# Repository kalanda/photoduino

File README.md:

_                          _       _             
          | |           _            | |     (_)            
     ____ | |__   ___ _| |_  ___   __| |_   _ _ ____   ___  
    |  _ \|  _ \ / _ (_   _)/ _ \ / _  | | | | |  _ \ / _ \ 
    | |_| | | | | |_| || |_| |_| ( (_| | |_| | | | | | |_| |
    |  __/|_| |_|\___/  \__)\___/ \____|____/|_|_| |_|\___/ 
    |_|  THE OPENSOURCE CAMERA CONTROLLER BASED ON ARDUINO                                                         

https://kalanda.github.io/photoduino/

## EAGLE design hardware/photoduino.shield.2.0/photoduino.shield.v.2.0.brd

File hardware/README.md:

_                          _       _             
          | |           _            | |     (_)            
     ____ | |__   ___ _| |_  ___   __| |_   _ _ ____   ___  
    |  _ \|  _ \ / _ (_   _)/ _ \ / _  | | | | |  _ \ / _ \ 
    | |_| | | | | |_| || |_| |_| ( (_| | |_| | | | | | |_| |
    |  __/|_| |_|\___/  \__)\___/ \____|____/|_|_| |_|\___/ 
    |_|  THE OPENSOURCE CAMERA CONTROLLER BASED ON ARDUINO                                                         

#Photoduino hardware

This is the repository for hardware parts of Photoduino.

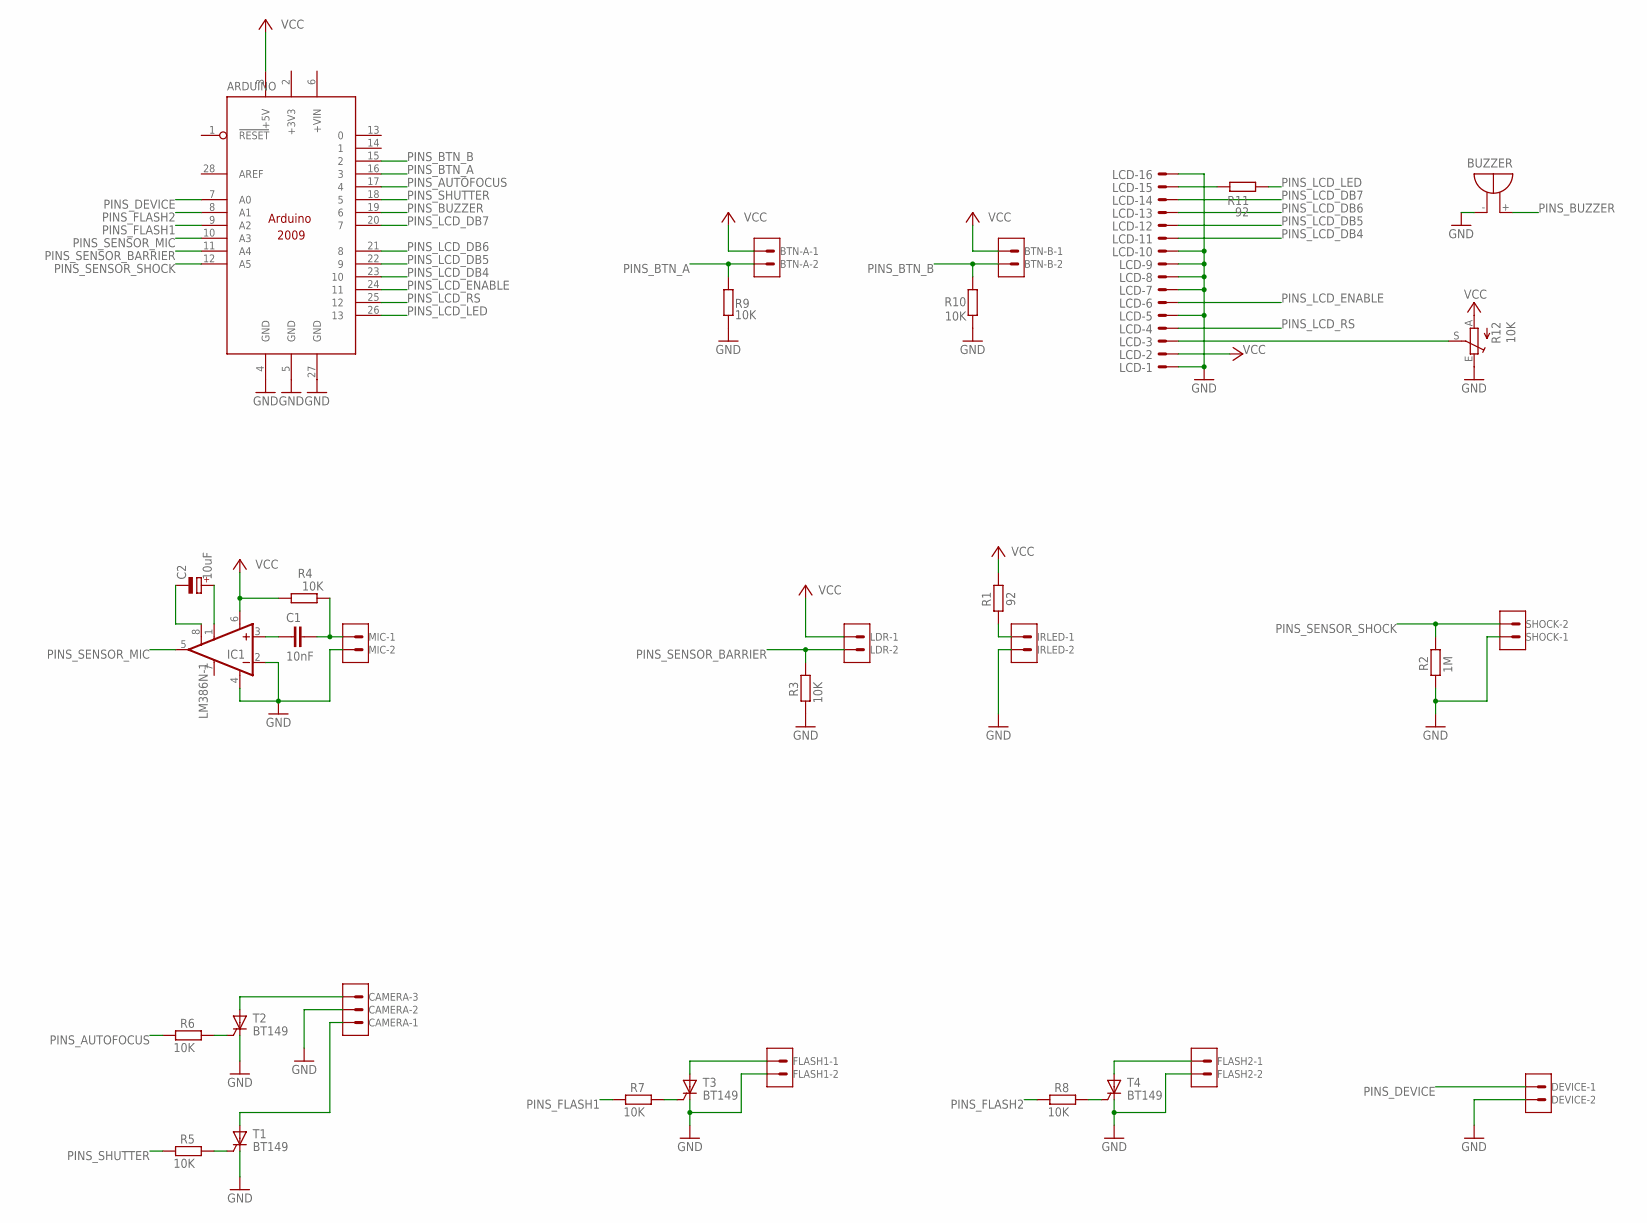
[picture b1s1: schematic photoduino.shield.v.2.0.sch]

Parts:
ARDUINO: ARDUINO2009_11; ARDUINO2009_1
BTN-A: 22-27-2021-02; 6410-02
BTN-B: 22-27-2021-02; 6410-02
BUZZER: F/TMB
C1: 10nF; C050-025X075
C2: 10uF; E2,5-6
CAMERA: 22-27-2031-03; 6410-03
DEVICE: 22-27-2021-02; 6410-02
FLASH1, FLASH2: 22-27-2021-02; 6410-02
IC1: LM386N-1; DIL08
IRLED: 22-27-2021-02; 6410-02
LCD: ML16E; ML16
LDR: 22-27-2021-02; 6410-02
LOGO: LOGOKALANDA
MIC: 22-27-2021-02; 6410-02
R1, R11: 92; 0207/7
R2: 1M; 0207/7
R3, R4, R5, R6, R7, R8, R9, R10: 10K; 0207/7
R12: 10K; RJ9W
SHOCK: 22-27-2021-02; 6410-02
T1, T2, T3, T4: BT149; TO92-4

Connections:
+3V3: ARDUINO.2 (+3V3)
GND: ARDUINO.4 (GND), ARDUINO.5 (GND), ARDUINO.27 (GND), BUZZER.-, CAMERA.2, DEVICE.2, FLASH1.2, FLASH2.2, IC1.2 (-IN), IC1.4 (GND), IRLED.2, LCD.1, LCD.5, LCD.7, LCD.8, LCD.9, LCD.10, LCD.16, MIC.2, R2.2, R3.2, R9.1, R10.2, R12.E, SHOCK.1, T1.C, T2.C, T3.C, T4.C
LCD_CONTRAST: LCD.3, R12.S
unnamed: IRLED.1, R1.2
unnamed: C1.1, IC1.3 (+IN)
unnamed: C1.2, MIC.1, R4.1
unnamed: R7.1, T3.G
unnamed: R8.1, T4.G
unnamed: CAMERA.3, T2.A
unnamed: R6.1, T2.G
unnamed: R5.1, T1.G
unnamed: C2.+, IC1.1 (GAIN)
unnamed: FLASH2.1, T4.A
unnamed: FLASH1.1, T3.A
unnamed: C2.-, IC1.8 (GAIN)
unnamed: LCD.15, R11.2
PINS_AUTOFOCUS: ARDUINO.17 (4), R6.2
PINS_BTN_A: ARDUINO.16 (3), BTN-A.2, R9.2
PINS_BTN_B: ARDUINO.15 (2), BTN-B.2, R10.1
PINS_BUZZER: ARDUINO.19 (6), BUZZER.+
PINS_DEVICE: ARDUINO.7 (A0), DEVICE.1
PINS_FLASH1: ARDUINO.9 (A2), R7.2
PINS_FLASH2: ARDUINO.8 (A1), R8.2
PINS_LCD_DB4: ARDUINO.23 (10), LCD.11
PINS_LCD_DB5: ARDUINO.22 (9), LCD.12
PINS_LCD_DB6: ARDUINO.21 (8), LCD.13
PINS_LCD_DB7: ARDUINO.20 (7), LCD.14
PINS_LCD_ENABLE: ARDUINO.24 (11), LCD.6
PINS_LCD_LED: ARDUINO.26 (13), R11.1
PINS_LCD_RS: ARDUINO.25 (12), LCD.4
PINS_SENSOR_BARRIER: ARDUINO.11 (A4), LDR.2, R3.1
PINS_SENSOR_MIC: ARDUINO.10 (A3), IC1.5 (OUT)
PINS_SENSOR_SHOCK: ARDUINO.12 (A5), R2.1, SHOCK.2
PINS_SHUTTER: ARDUINO.18 (5), R5.2
SHUTTER: CAMERA.1, T1.A
VCC: ARDUINO.3 (+5V), BTN-A.1, BTN-B.1, IC1.6 (VS), LCD.2, LDR.1, R1.1, R4.2, R12.A

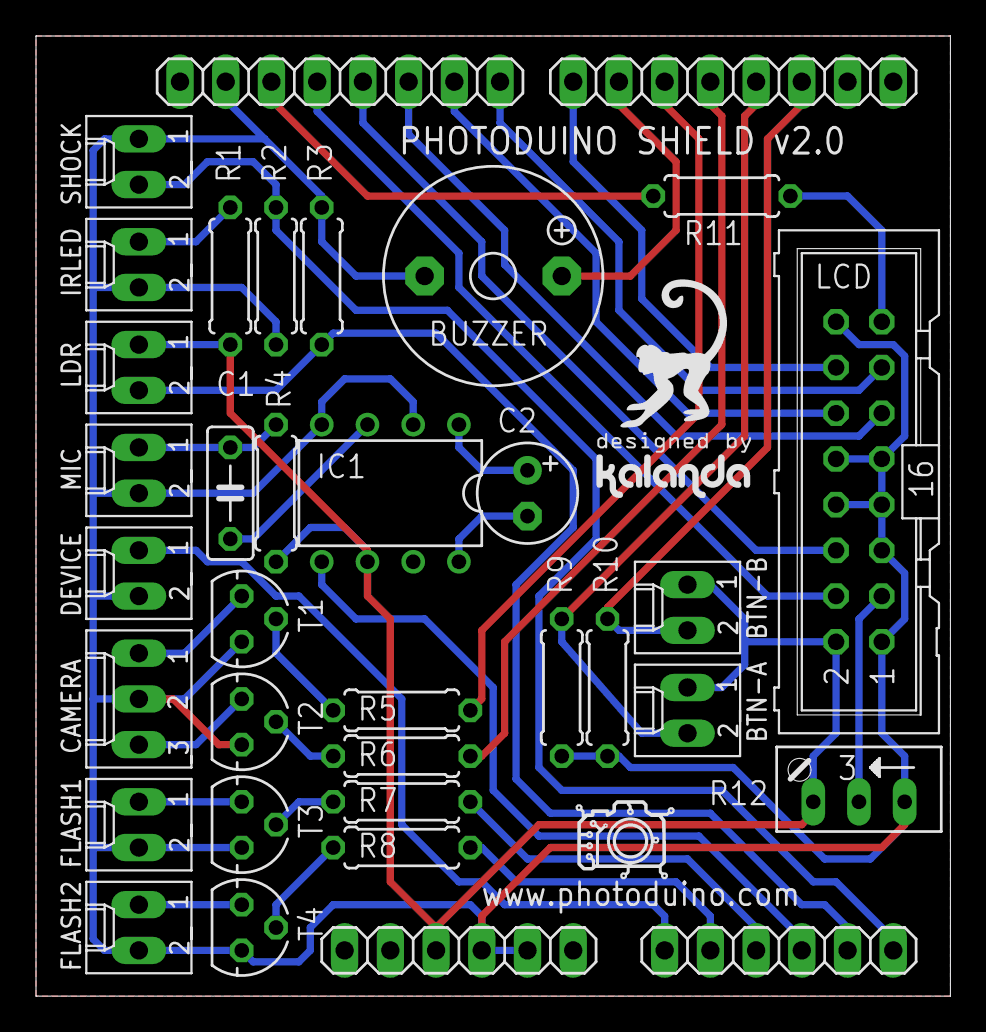
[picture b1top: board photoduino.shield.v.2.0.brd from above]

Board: 2 copper layers, 50.8 x 53.3 mm, 34 parts (0 on the bottom side), 35 nets.

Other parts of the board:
U$1: LOGOPHOTODUINO

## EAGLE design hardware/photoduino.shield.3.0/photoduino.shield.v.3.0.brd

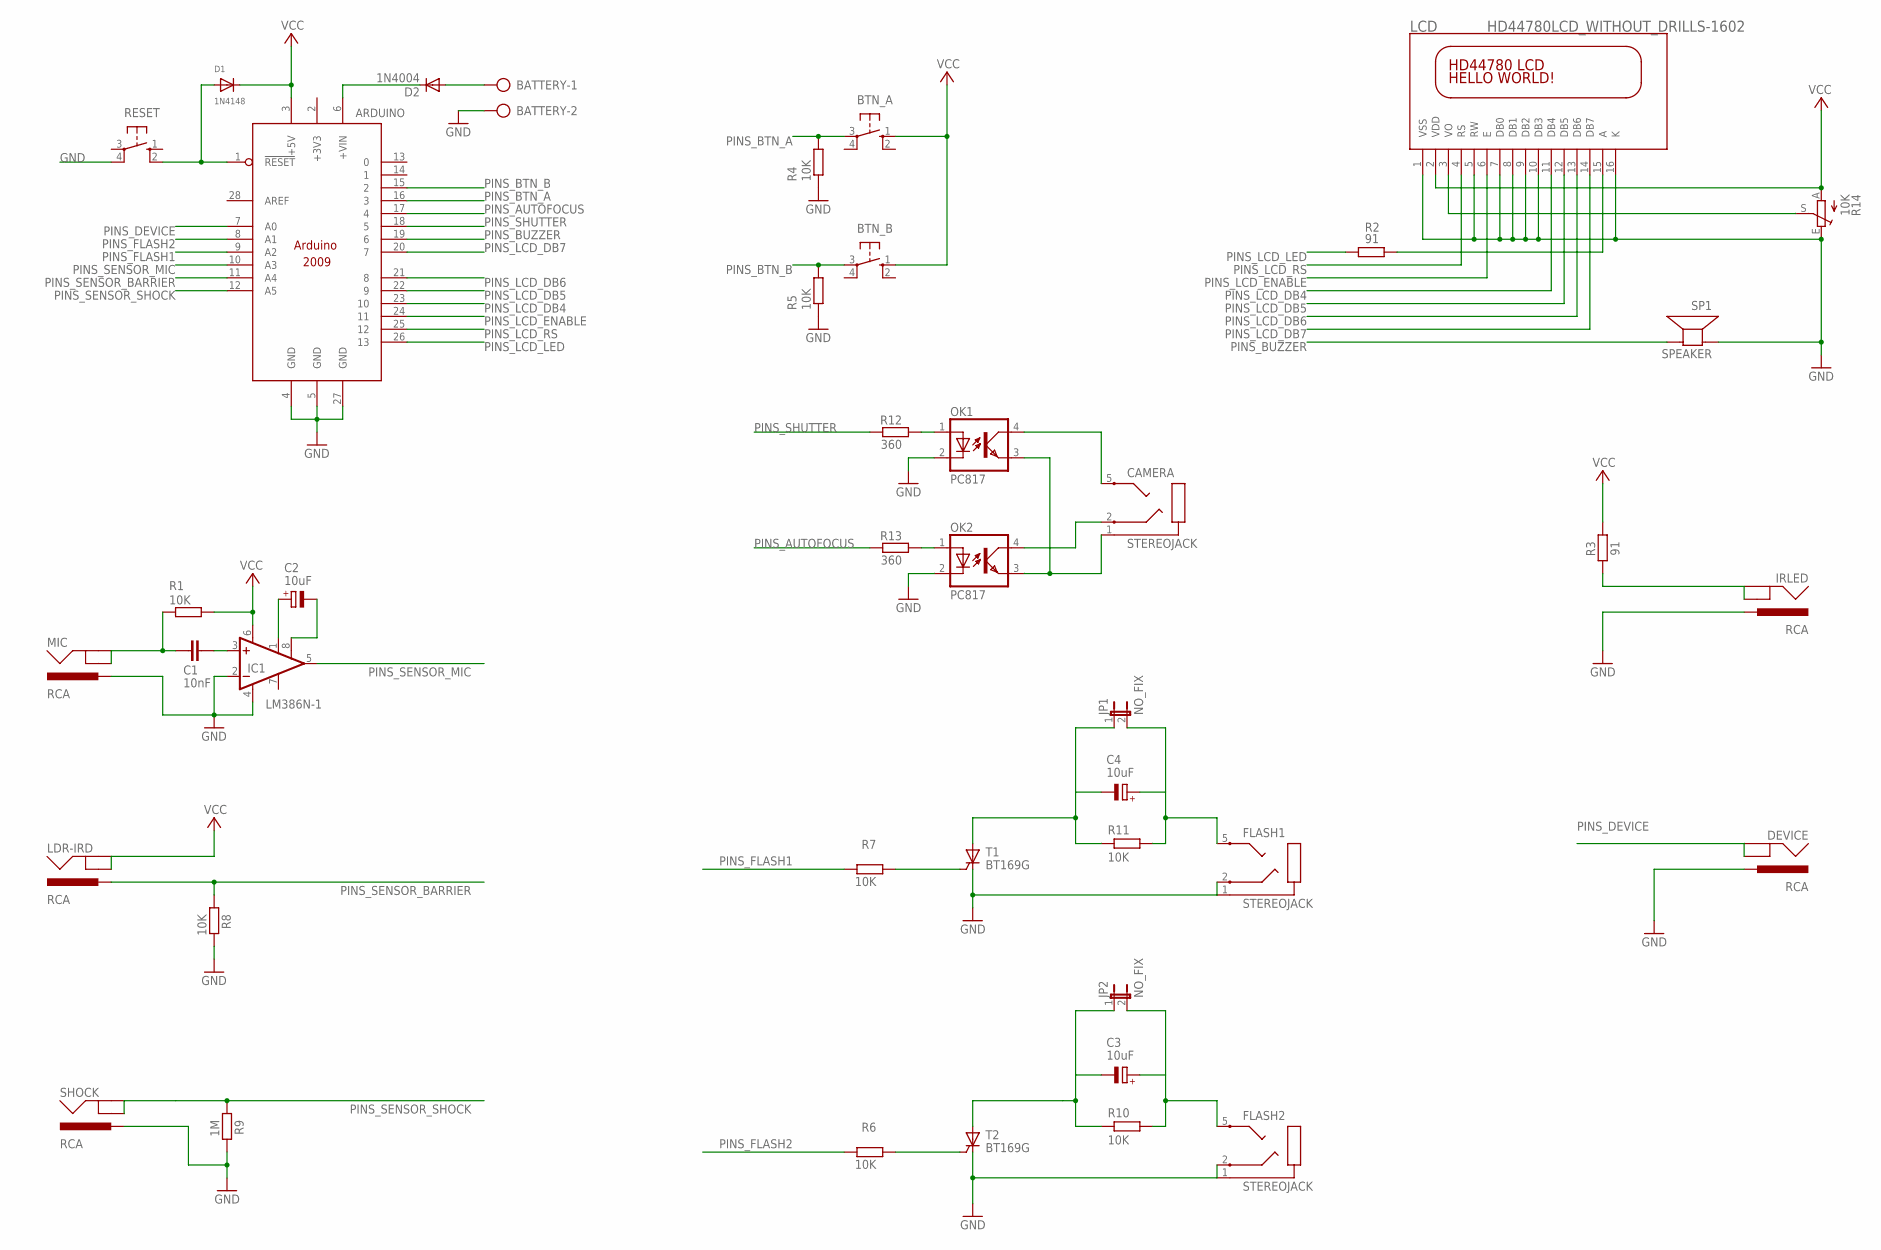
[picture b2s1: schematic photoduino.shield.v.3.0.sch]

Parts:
ARDUINO: ARDUINO2009_12; ARDUINO2009_2
BATTERY: AK500/2
BTN_A: 10-XX; B3F-10XX
BTN_B: 10-XX; B3F-10XX
C1: 10nF; C050-025X075
C2, C3, C4: 10uF; E2,5-7
CAMERA: STEREOJACK; STX3100-3N
D1: 1N4148; DO-1N4148
D2: 1N4004; DO41-10
DEVICE: RCA; RCA_4UCON
FLASH1, FLASH2: STEREOJACK; STX3100-3N
IC1: LM386N-1; DIL08
IRLED: RCA; RCA_4UCON
JP1, JP2: NO_FIX; JP1
LCD: HD44780LCD_WITHOUT_DRILLS-1602; LCD1602
LDR-IRD: RCA; RCA_4UCON
MIC: RCA; RCA_4UCON
OK1, OK2: PC817; DIL04
R1, R4, R5, R6, R7, R8, R10, R11: 10K; 0207/7
R2, R3: 91; 0207/7
R9: 1M; 0207/7
R12, R13: 360; 0207/7
R14: 10K; B25U
RESET: 10-XX; B3F-10XX
SHOCK: RCA; RCA_4UCON
SP1: SPEAKER; PS12
T1, T2: BT169G; TO92-2

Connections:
+3V3: ARDUINO.2 (+3V3)
GND: ARDUINO.4 (GND), ARDUINO.5 (GND), ARDUINO.27 (GND), BATTERY.2, DEVICE.BARREL, FLASH1.1, FLASH1.2, FLASH2.1, FLASH2.2, IC1.2 (-IN), IC1.4 (GND), IRLED.BARREL, LCD.1 (VSS), LCD.5 (RW), LCD.7 (DB0), LCD.8 (DB1), LCD.9 (DB2), LCD.10 (DB3), LCD.16 (K), MIC.BARREL, OK1.2 (C), OK2.2 (C), R4.1, R5.1, R8.2, R9.2, R14.E, RESET.4 (P1), SHOCK.BARREL, SP1.P$1 (+), T1.C, T2.C
LCD_CONTRAST: LCD.3 (VO), R14.S
unnamed: IRLED.BREAK, IRLED.SPRING, R3.2
unnamed: CAMERA.1, OK1.3 (EMIT), OK2.3 (EMIT)
unnamed: C4.+, FLASH1.5, JP1.2, R11.2
unnamed: R6.1, T2.G
unnamed: ARDUINO.1 (!RESET), D1.A, RESET.2 (S1)
unnamed: C4.-, JP1.1, R11.1, T1.A
unnamed: C3.+, FLASH2.5, JP2.2, R10.2
unnamed: C3.-, JP2.1, R10.1, T2.A
unnamed: ARDUINO.6 (+VIN), D2.C
unnamed: C1.1, IC1.3 (+IN)
unnamed: BATTERY.1, D2.A
unnamed: C1.2, MIC.BREAK, MIC.SPRING, R1.1
unnamed: R7.1, T1.G
unnamed: CAMERA.5, OK1.4 (COL)
unnamed: OK1.1 (A), R12.1
unnamed: OK2.1 (A), R13.1
unnamed: C2.+, IC1.1 (GAIN)
unnamed: C2.-, IC1.8 (GAIN)
unnamed: LCD.15 (A), R2.1
PINS_AUTOFOCUS: ARDUINO.17 (4), R13.2
PINS_BTN_A: ARDUINO.16 (3), BTN_A.3, R4.2
PINS_BTN_B: ARDUINO.15 (2), BTN_B.3, R5.2
PINS_BUZZER: ARDUINO.19 (6), SP1.P$2 (-)
PINS_DEVICE: ARDUINO.7 (A0), DEVICE.BREAK, DEVICE.SPRING
PINS_FLASH1: ARDUINO.9 (A2), R7.2
PINS_FLASH2: ARDUINO.8 (A1), R6.2
PINS_LCD_DB4: ARDUINO.23 (10), LCD.11 (DB4)
PINS_LCD_DB5: ARDUINO.22 (9), LCD.12 (DB5)
PINS_LCD_DB6: ARDUINO.21 (8), LCD.13 (DB6)
PINS_LCD_DB7: ARDUINO.20 (7), LCD.14 (DB7)
PINS_LCD_ENABLE: ARDUINO.24 (11), LCD.6 (E)
PINS_LCD_LED: ARDUINO.26 (13), R2.2
PINS_LCD_RS: ARDUINO.25 (12), LCD.4 (RS)
PINS_SENSOR_BARRIER: ARDUINO.11 (A4), LDR-IRD.BARREL, R8.1
PINS_SENSOR_MIC: ARDUINO.10 (A3), IC1.5 (OUT)
PINS_SENSOR_SHOCK: ARDUINO.12 (A5), R9.1, SHOCK.BREAK, SHOCK.SPRING
PINS_SHUTTER: ARDUINO.18 (5), R12.2
SHUTTER: CAMERA.2, OK2.4 (COL)
VCC: ARDUINO.3 (+5V), BTN_A.1 (S), BTN_B.1 (S), D1.C, IC1.6 (VS), LCD.2 (VDD), LDR-IRD.BREAK, LDR-IRD.SPRING, R1.2, R3.1, R14.A

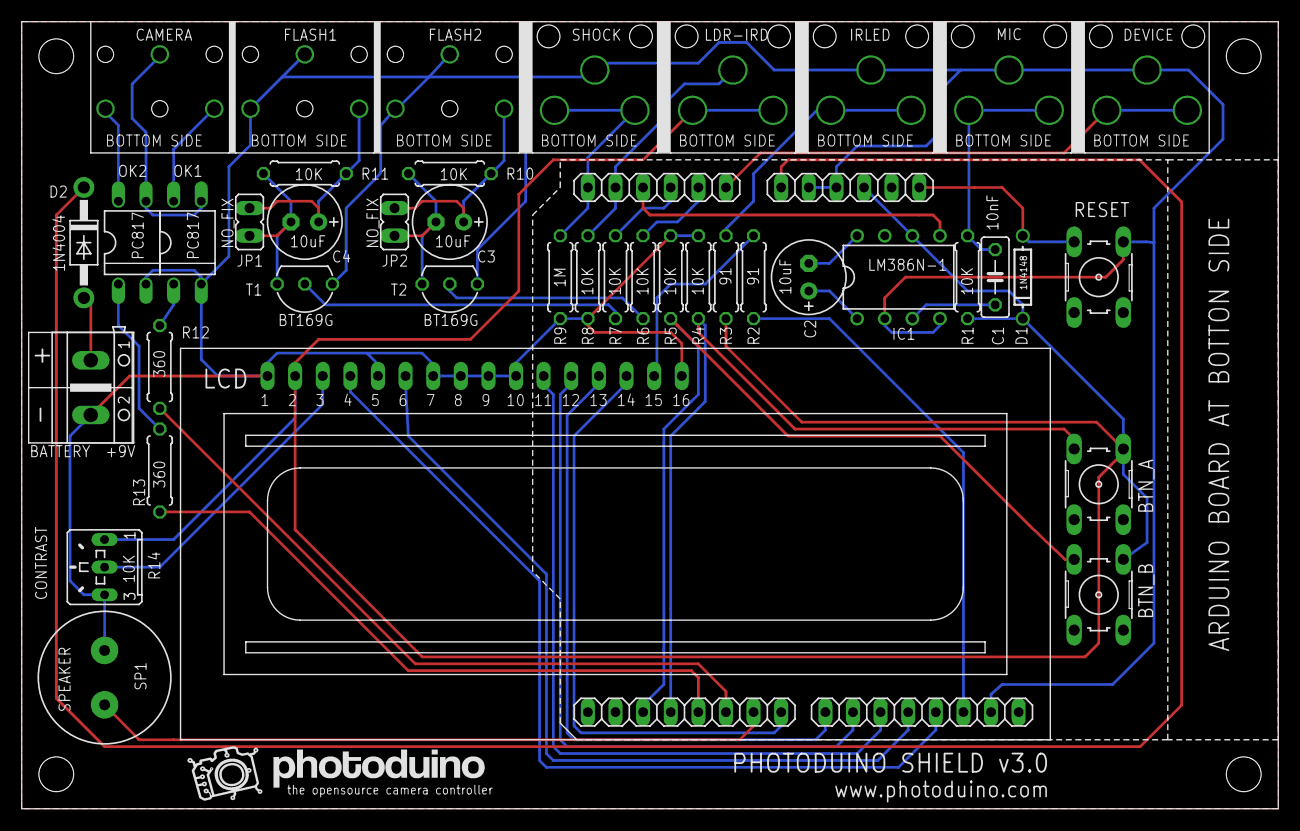
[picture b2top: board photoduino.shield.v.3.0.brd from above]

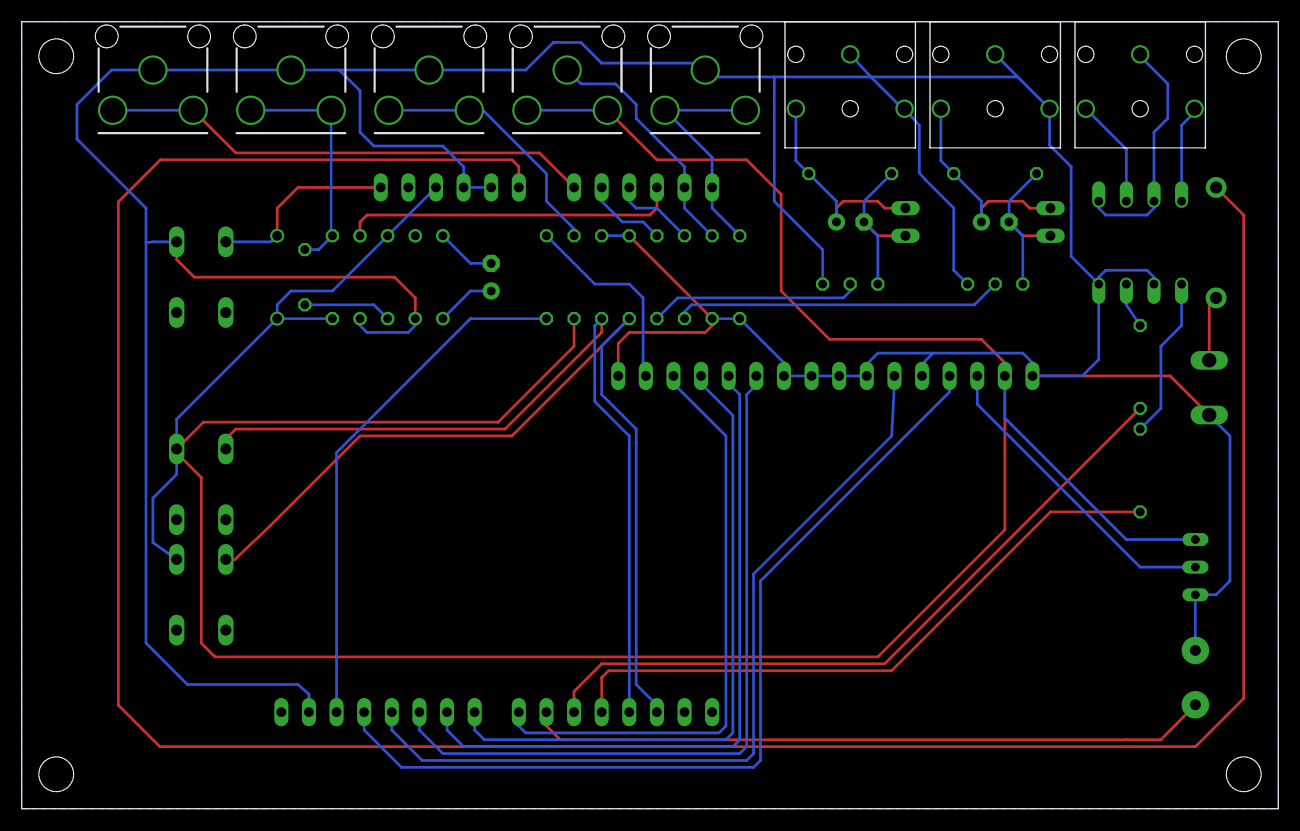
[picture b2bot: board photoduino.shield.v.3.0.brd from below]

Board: 2 copper layers, 115.6 x 72.4 mm, 43 parts (8 on the bottom side), 41 nets.

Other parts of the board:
U$2: LOGOPHOTODUINO2

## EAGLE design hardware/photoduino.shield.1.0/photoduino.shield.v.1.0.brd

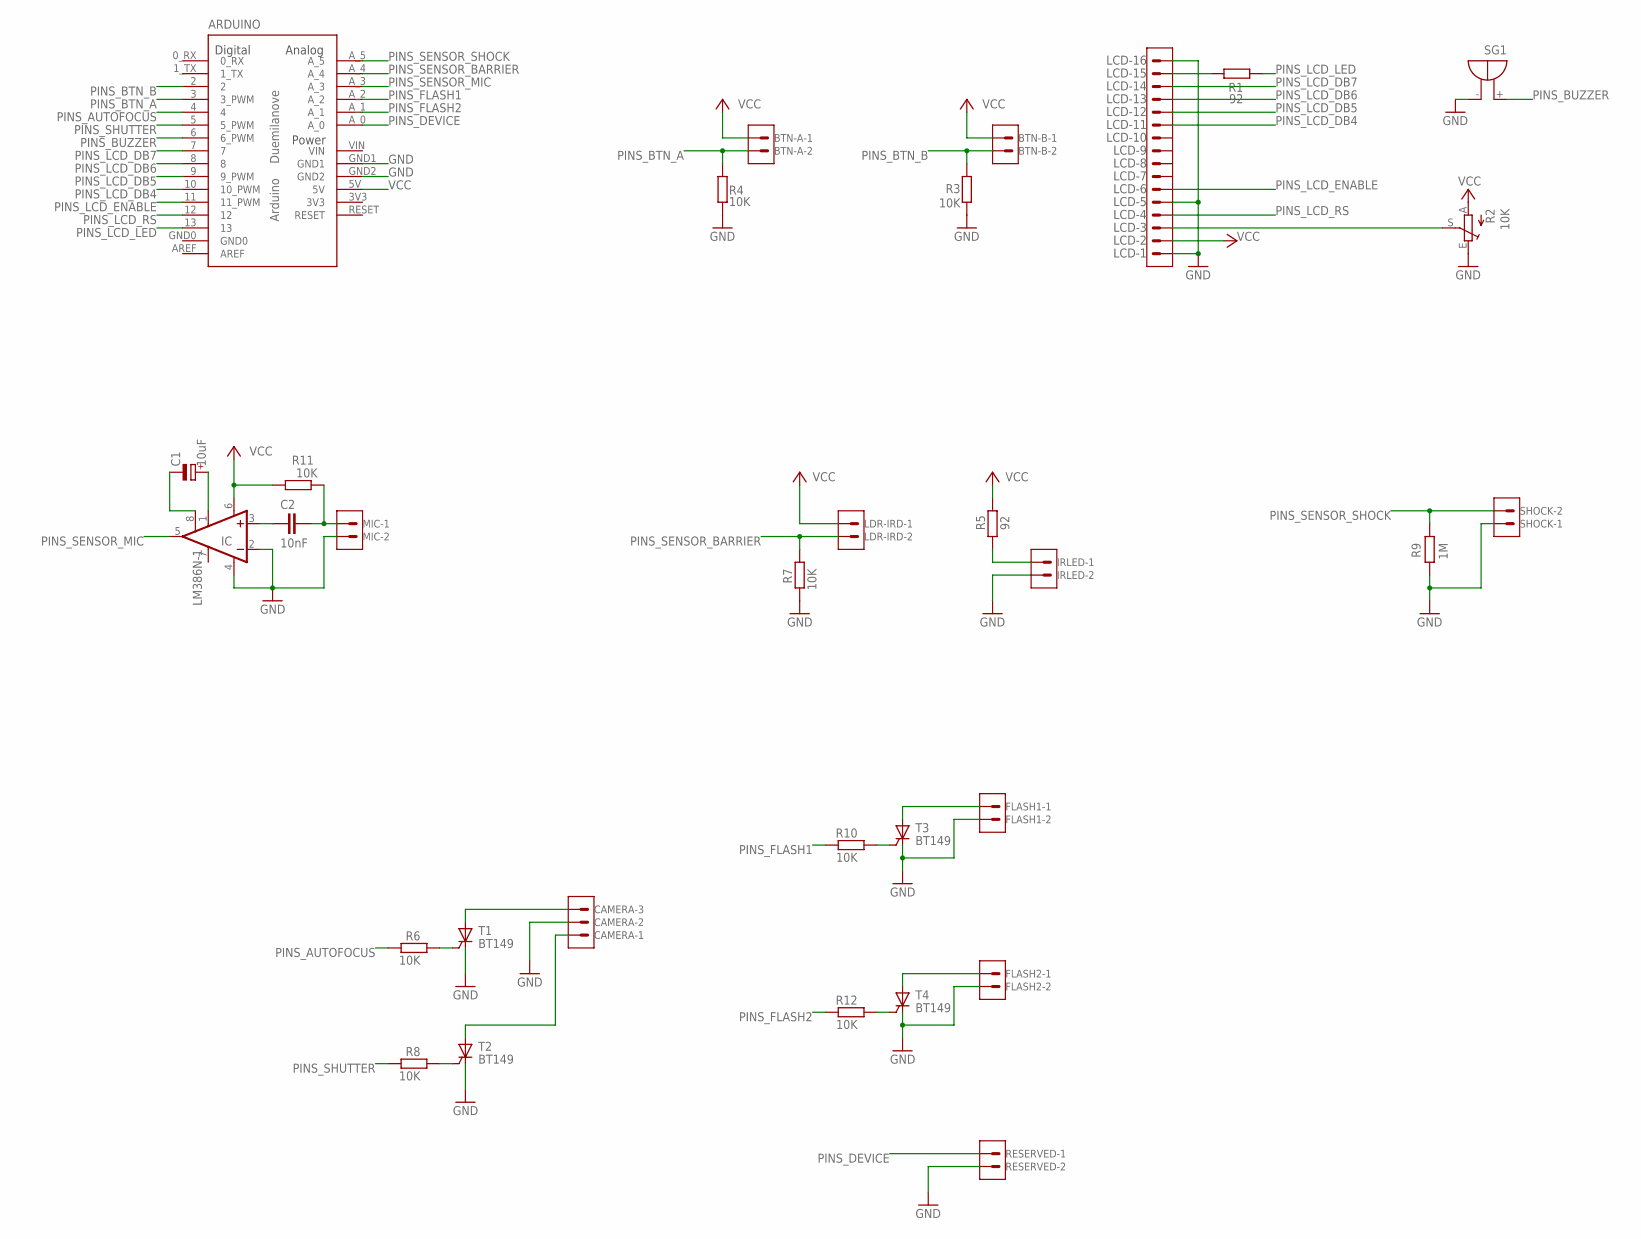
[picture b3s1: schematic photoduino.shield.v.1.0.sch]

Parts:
ARDUINO: ARDUINO-USBNO-OUTLINE-NO-TEXT-OCTAGONAL; NO-OUTLINE-OCTAGONAL-NOTEXT
BTN-A: 22-27-2021-02; 6410-02
BTN-B: 22-27-2021-02; 6410-02
C1: 10uF; E2,5-6
C2: 10nF; C050-025X075
CAMERA: 22-27-2031-03; 6410-03
FLASH1, FLASH2: 22-27-2021-02; 6410-02
IC: LM386N-1; DIL08
IRLED: 22-27-2021-02; 6410-02
LCD: HD44780; ML16
LDR-IRD: 22-27-2021-02; 6410-02
MIC: 22-27-2021-02; 6410-02
R1: 92; 0207/10
R2: 10K; RJ9W
R3, R4, R7, R11: 10K; 0207/7
R5: 92; 0207/7
R6, R8, R10, R12: 10K; 0309V
R9: 1M; 0309V
RESERVED: 22-27-2021-02; 6410-02
SG1: F/TMB
SHOCK: 22-27-2021-02; 6410-02
T1, T2, T3, T4: BT149; TO92-4

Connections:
3V3: ARDUINO.3V3
GND: ARDUINO.GND1, ARDUINO.GND2, CAMERA.2, FLASH1.2, FLASH2.2, IC.2 (-IN), IC.4 (GND), IRLED.2, LCD.1, LCD.5, LCD.16, MIC.2, R2.E, R3.2, R4.1, R7.2, R9.1, RESERVED.2, SG1.-, SHOCK.1, T1.C, T2.C, T3.C, T4.C
LCD_CONTRAST: LCD.3, R2.S
unnamed: C2.1, IC.3 (+IN)
unnamed: C2.2, MIC.1, R11.1
unnamed: IRLED.1, R5.1
unnamed: R10.1, T3.G
unnamed: R12.1, T4.G
unnamed: CAMERA.3, T1.A
unnamed: R6.1, T1.G
unnamed: R8.1, T2.G
unnamed: C1.+, IC.1 (GAIN)
unnamed: FLASH2.1, T4.A
unnamed: FLASH1.1, T3.A
unnamed: C1.-, IC.8 (GAIN)
unnamed: LCD.15, R1.2
PINS_AUTOFOCUS: ARDUINO.4, R6.2
PINS_BTN_A: ARDUINO.3 (3_PWM), BTN-A.2, R4.2
PINS_BTN_B: ARDUINO.2, BTN-B.2, R3.1
PINS_BUZZER: ARDUINO.6 (6_PWM), SG1.+
PINS_DEVICE: ARDUINO.A_0, RESERVED.1
PINS_FLASH1: ARDUINO.A_2, R10.2
PINS_FLASH2: ARDUINO.A_1, R12.2
PINS_LCD_DB4: ARDUINO.10 (10_PWM), LCD.11
PINS_LCD_DB5: ARDUINO.9 (9_PWM), LCD.12
PINS_LCD_DB6: ARDUINO.8, LCD.13
PINS_LCD_DB7: ARDUINO.7, LCD.14
PINS_LCD_ENABLE: ARDUINO.11 (11_PWM), LCD.6
PINS_LCD_LED: ARDUINO.13, R1.1
PINS_LCD_RS: ARDUINO.12, LCD.4
PINS_SENSOR_BARRIER: ARDUINO.A_4, LDR-IRD.2, R7.1
PINS_SENSOR_MIC: ARDUINO.A_3, IC.5 (OUT)
PINS_SENSOR_SHOCK: ARDUINO.A_5, R9.2, SHOCK.2
PINS_SHUTTER: ARDUINO.5 (5_PWM), R8.2
SHUTTER: CAMERA.1, T2.A
VCC: ARDUINO.5V, BTN-A.1, BTN-B.1, IC.6 (VS), LCD.2, LDR-IRD.1, R2.A, R5.2, R11.2
VIN: ARDUINO.VIN

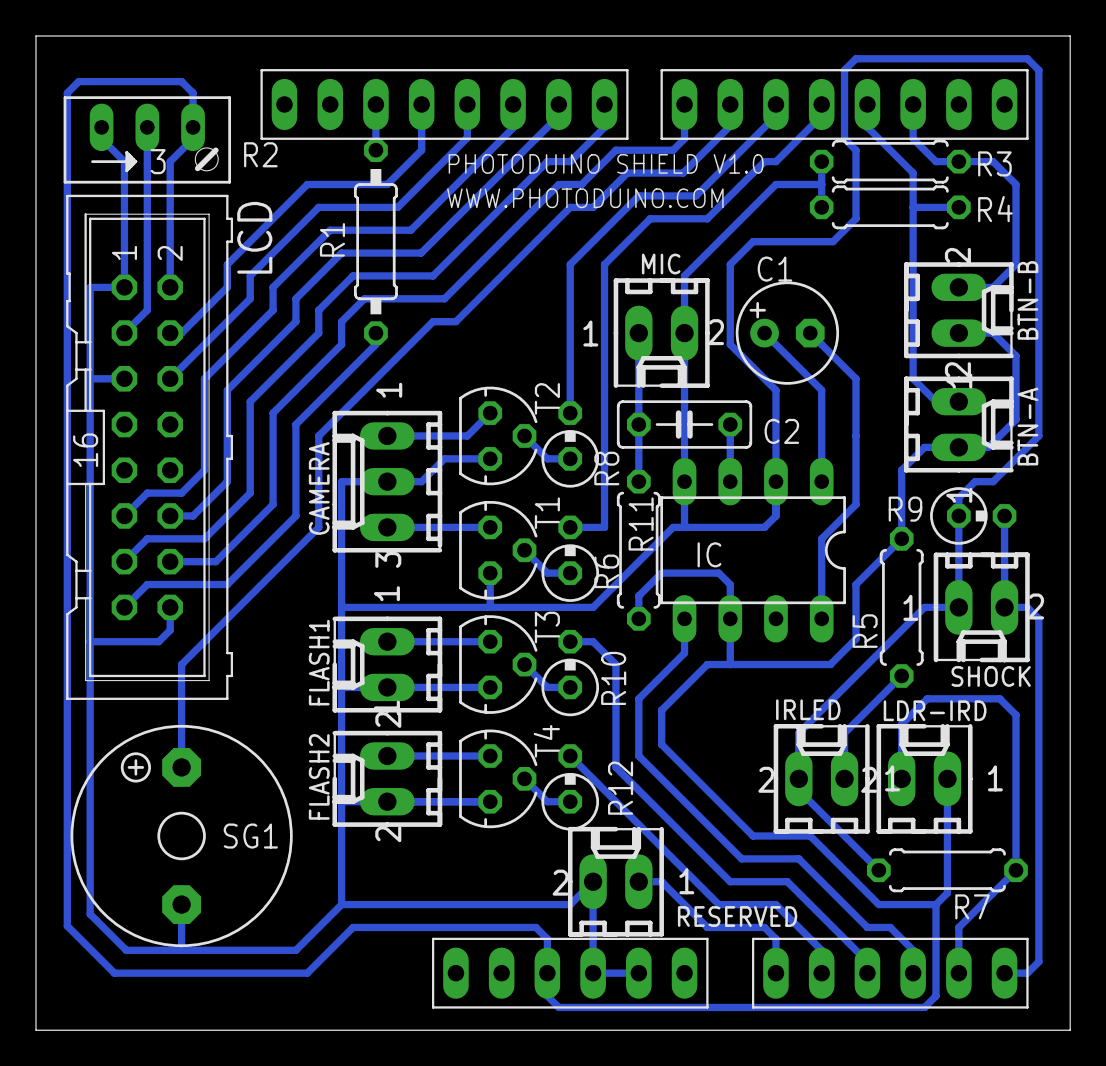
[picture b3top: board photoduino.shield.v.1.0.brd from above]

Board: 2 copper layers, 57.5 x 55.2 mm, 32 parts (0 on the bottom side), 35 nets.

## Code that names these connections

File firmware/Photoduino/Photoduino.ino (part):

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#define LCD_ROWS             2  // rows

// Pinout settings
#define PINS_LCD_LED         13 //(digital pin)
#define PINS_LCD_RS          12 //(digital pin)
#define PINS_LCD_ENABLE      11 //(digital pin)
#define PINS_LCD_DB4         10 //(digital pin)
#define PINS_LCD_DB5         9  //(digital pin)
#define PINS_LCD_DB6         8  //(digital pin)
#define PINS_LCD_DB7         7  //(digital pin)
#define PINS_BUZZER          6  //(digital pin with pwm)
#define PINS_SHUTTER         5  //(digital pin)
#define PINS_AUTOFOCUS       4  //(digital pin)
#define PINS_BTN_A           3  //(digital pin)
#define PINS_BTN_B           2  //(digital pin)

#define PINS_SENSOR_SHOCK    5  //(analog pin)
#define PINS_SENSOR_BARRIER  4  //(analog pin)
#define PINS_SENSOR_MIC      3  //(analog pin)

#ifdef BOARD_ARDUINO_MEGA    // For ArduinoMega compatibility
  #define PINS_FLASH1        56 // Mega pin 56 = Duemilanove 16 (digital pin)
  #define PINS_FLASH2        55 // Mega pin 55 = Duemilanove 15 (digital pin)
  #define PINS_DEVICE        54 // Mega pin 54 = Duemilanove 14 (digital pin)
#else  
  #define PINS_FLASH1        16 //(digital pin)
  #define PINS_FLASH2        15 //(digital pin)
  #define PINS_DEVICE        14 //(digital pin)
#endif

#define PINS_LASER           PINS_DEVICE  // alias(digital pin)
#define PINS_SOLENOID_VALVE  PINS_DEVICE  // alias(digital pin)

// Sensor types
#define SENSOR_TYPE_NONE                 0 // None sensor
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#include LANGUAGE_FILE     // Messages

// LiquidCrystal LCD control object instance
LiquidCrystal lcd(PINS_LCD_RS, PINS_LCD_ENABLE, PINS_LCD_DB4, PINS_LCD_DB5, PINS_LCD_DB6, PINS_LCD_DB7);

// Variables used on interrupt mode
volatile boolean cancelFlag = false;    // Flag used to abort interrupt mode
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  lcd.createChar(SYMBOL_UP, char_arrow_up);

  // Pinmode inputs
  pinMode(PINS_BTN_A,          INPUT);     
  pinMode(PINS_BTN_B,          INPUT);    
  pinMode(PINS_SENSOR_SHOCK,   INPUT); 
  pinMode(PINS_SENSOR_BARRIER, INPUT);
  pinMode(PINS_SENSOR_MIC,     INPUT);  

  // Pinmode outputs
  pinMode(PINS_SHUTTER,        OUTPUT);
  pinMode(PINS_AUTOFOCUS,      OUTPUT);
  pinMode(PINS_FLASH1,         OUTPUT);
  pinMode(PINS_FLASH2,         OUTPUT);
  pinMode(PINS_LCD_LED,        OUTPUT);
  pinMode(PINS_LCD_RS,         OUTPUT);
  pinMode(PINS_LCD_ENABLE,     OUTPUT);
  pinMode(PINS_LCD_DB4,        OUTPUT);
  pinMode(PINS_LCD_DB5,        OUTPUT);
  pinMode(PINS_LCD_DB6,        OUTPUT);
  pinMode(PINS_LCD_DB7,        OUTPUT);
  pinMode(PINS_BUZZER,         OUTPUT);
  pinMode(PINS_DEVICE,         OUTPUT);
  
  // Init Firmata 
  FirmataLite.attach(START_SYSEX, sysexCallback);
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
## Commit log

2014-10-12 Added logos and case files
2015-01-25 Added a statusbar for the intervallometer
2015-05-23 Fixed CODE_MINOR_VERSION to the real version (1.1)
2015-06-10 Add logo without text
2016-04-11 Added gh-pages
2016-04-11 Added CNAME
2016-04-11 Update CNAME
2016-04-11 Added cookiebanner and GA
2016-04-11 Documentation fixes
2016-04-11 GA fixes
2018-05-17 Create CNAME
2018-07-03 Removed analytics and cookies
2019-02-10 Added function prototypes to fix latest Arduino IDE compilation errors
2019-06-05 Jekyll site source
2019-06-05 Force rebuild
2019-06-05 permalink: /404.html
2019-06-05 Fix tables
2020-02-22 Moving out from domain
2020-03-22 Moving out from sourceforge
2021-08-06 Added videos to repo
2021-08-06 Added video subs
2021-08-06 HTML5 videos and fix invalid chars
2021-08-06 Use videos from final domain

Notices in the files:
firmware/Photoduino/Photoduino.ino:
Photoduino is free software: you can redistribute it and/or modify
it under the terms of the GNU General Public License as published by
the Free Software Foundation, either version 3 of the License, or
(at your option) any later version.
hardware/photoduino.shield.2.0/photoduino.shield.v.2.0.sch:
Licensed under GNU General Public Licence v3
